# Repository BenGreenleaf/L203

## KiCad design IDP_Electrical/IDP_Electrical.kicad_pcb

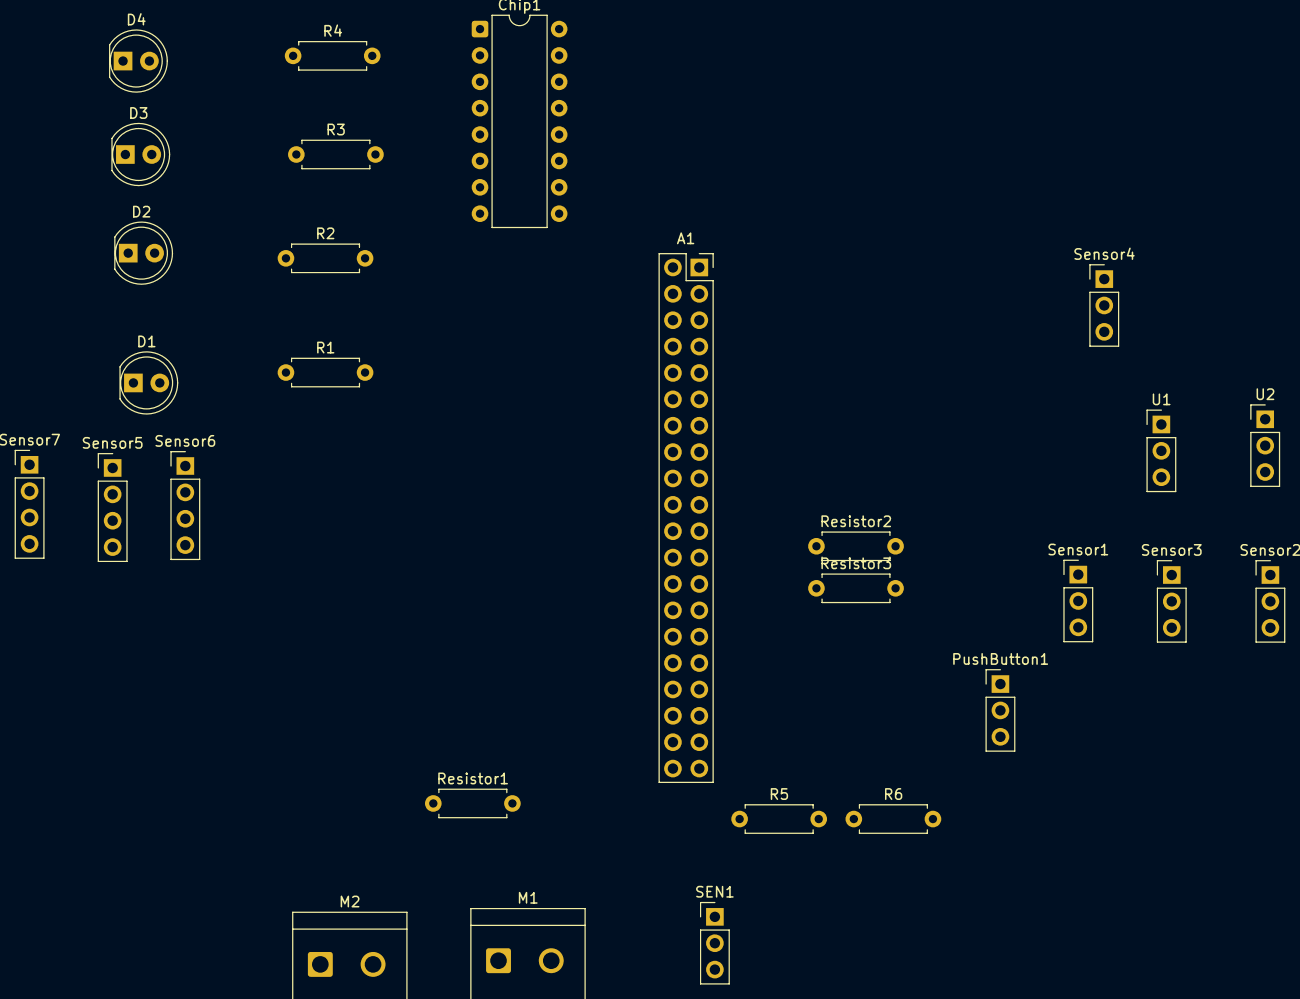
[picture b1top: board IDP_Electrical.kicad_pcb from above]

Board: 2 copper layers, 28 parts (0 on the bottom side), 12 nets, no tracks yet.

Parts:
A1: PicoBot; PinSocket_2x20_P2.54mm_Vertical
Chip1: Optocoupler_ACPL-847-000E; DIP-16_W7.62mm
D1: Green LED; LED_D5.0mm
D2: Red LED; LED_D5.0mm
D3: Yellow LED; LED_D5.0mm
D4: Blue LED; LED_D5.0mm
M1, M2: DC Motor Symbol; TerminalBlock_CUI_TB007-508-02_1x02_P5.08mm_Horizontal
PushButton1: PinHeader_1x03_P2.54mm_Vertical
R1, R2, R3, R4: 480; R_Axial_DIN0207_L6.3mm_D2.5mm_P7.62mm_Horizontal
R5: 2.2k; R_Axial_DIN0207_L6.3mm_D2.5mm_P7.62mm_Horizontal
R6: R_test; R_Axial_DIN0207_L6.3mm_D2.5mm_P7.62mm_Horizontal
Resistor1, Resistor2, Resistor3: Test; R_Axial_DIN0207_L6.3mm_D2.5mm_P7.62mm_Horizontal
SEN1: PinHeader_1x03_P2.54mm_Vertical
Sensor1, Sensor2, Sensor3, Sensor4: SEN0017; PinHeader_1x03_P2.54mm_Vertical
Sensor5, Sensor6, Sensor7: TMF8701; PinHeader_1x04_P2.54mm_Vertical
U1, U2: SER0038; PinHeader_1x03_P2.54mm_Vertical

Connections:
+3V3: D4.2 (A), PushButton1.2 (3V3_Power), R6.2, Resistor1.2, Resistor2.2, Resistor3.2, SEN1.2 (3V3_Red), Sensor1.2 (3V3_Power_Red), Sensor2.2 (3V3_Power_Red), Sensor3.2 (3V3_Power_Red), Sensor4.2 (3V3_Power_Red), Sensor5.4 (3V3_Power_Red), Sensor6.4 (3V3_Power_Red), Sensor7.4 (3V3_Power_Red)
GND: Chip1.2, Chip1.3, Chip1.7, Chip1.15, PushButton1.3 (GND), R5.1, SEN1.1 (GND_Black), Sensor1.3 (GND_Black), Sensor2.3 (GND_Black), Sensor3.3 (GND_Black), Sensor4.3 (GND_Black), Sensor5.3 (GND_Black), Sensor6.3 (GND_Black), Sensor7.3 (GND_Black), U1.1 (GND), U2.1 (GND)
unnamed: A1.1 (Servo_2_PWM), A1.17 (GPIO13_and_Servo_2_PWM)
unnamed: Chip1.1, R3.1
unnamed: D1.2 (A), Resistor1.1
unnamed: Chip1.16, D1.1 (K)
unnamed: D2.2 (A), Resistor2.1
unnamed: Chip1.8, D2.1 (K)
unnamed: D3.2 (A), Resistor3.1
unnamed: R5.2, R6.1
unnamed: Sensor5.2 (Clock_Blue), Sensor6.2 (Clock_Blue), Sensor7.2 (Clock_Blue)
unnamed: Sensor5.1 (Data_Green), Sensor6.1 (Data_Green), Sensor7.1 (Data_Green)

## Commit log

2026-02-23 File renaming
2026-02-23 Function renaming
2026-02-23 Updated schematic
2026-02-23 updated testing of sensors and servos
2026-02-23 initial, basic motor control
2026-02-23 initial rough motor and sensor logic
2026-02-24 updating
2026-02-24 added 480 ohmn R to optocoupler
2026-02-24 Footnote assigned in Schematics and PCB generated (with warnings)
2026-02-25 line following
2026-02-25 added motor testing
2026-02-25 Updated LED testing
2026-02-25 Some framework path finding functions
2026-02-25 fixing line logic
2026-02-26 line follwoing updates (broken rn)
2026-02-26 Path finding changes
2026-02-26 added US, LED GPIO correction
2026-02-26 Added US, updated LED GPIO
2026-02-26 updating motor control
2026-02-27 (broken) motor control update
2026-02-27 fixes
2026-02-27 Corner handling improvements
2026-03-03 updated circuitry on R_test
2026-03-03 line following fixed
2026-03-03 added a new cornering method - needs testing
2026-03-04 updated PCB
2026-03-04 4.3.26
2026-03-04 potential fix to line following
2026-03-04 undoing
2026-03-04 Greenleaf's Current changes
2026-03-05 Updated cornering tuning
2026-03-05 Further tuning to test today
2026-03-05 updated power and ground
2026-03-05 Further tuning and updates
2026-03-06 Buggy 180 turning with fixes still to be made
2026-03-06 Various 180 adjustments but still fails :(
2026-03-07 various edits
2026-03-07 rough architecture for main logic
2026-03-09 Map updates
2026-03-09 Further path following updates
2026-03-10 Ish working node finding
2026-03-10 working on scanning/deposit
2026-03-10 updated path
2026-03-11 additions to final code
2026-03-11 testing
2026-03-11 deposit updates
2026-03-11 Servo changes
2026-03-11 deposit fix
2026-03-11 11.3.26
2026-03-11 Sensors not working :(
2026-03-12 Really good line following and cornering
2026-03-12 sensors being annoying
2026-03-12 fixed distance sensor
2026-03-12 updated schematic wiring
2026-03-12 sensor testing
2026-03-12 Front sensor now working (had to edit some things to main to get it printing) (flags to true)
2026-03-13 Ben's suggested edits for loading bay (simplified). To test further post lectures today
2026-03-13 Updated work on bay collection
2026-03-13 resistance testing
2026-03-16 Turning delay with timing
2026-03-16 line following updates
2026-03-16 Some fixes with line following
2026-03-17 final updates i pray
2026-03-22 final code
